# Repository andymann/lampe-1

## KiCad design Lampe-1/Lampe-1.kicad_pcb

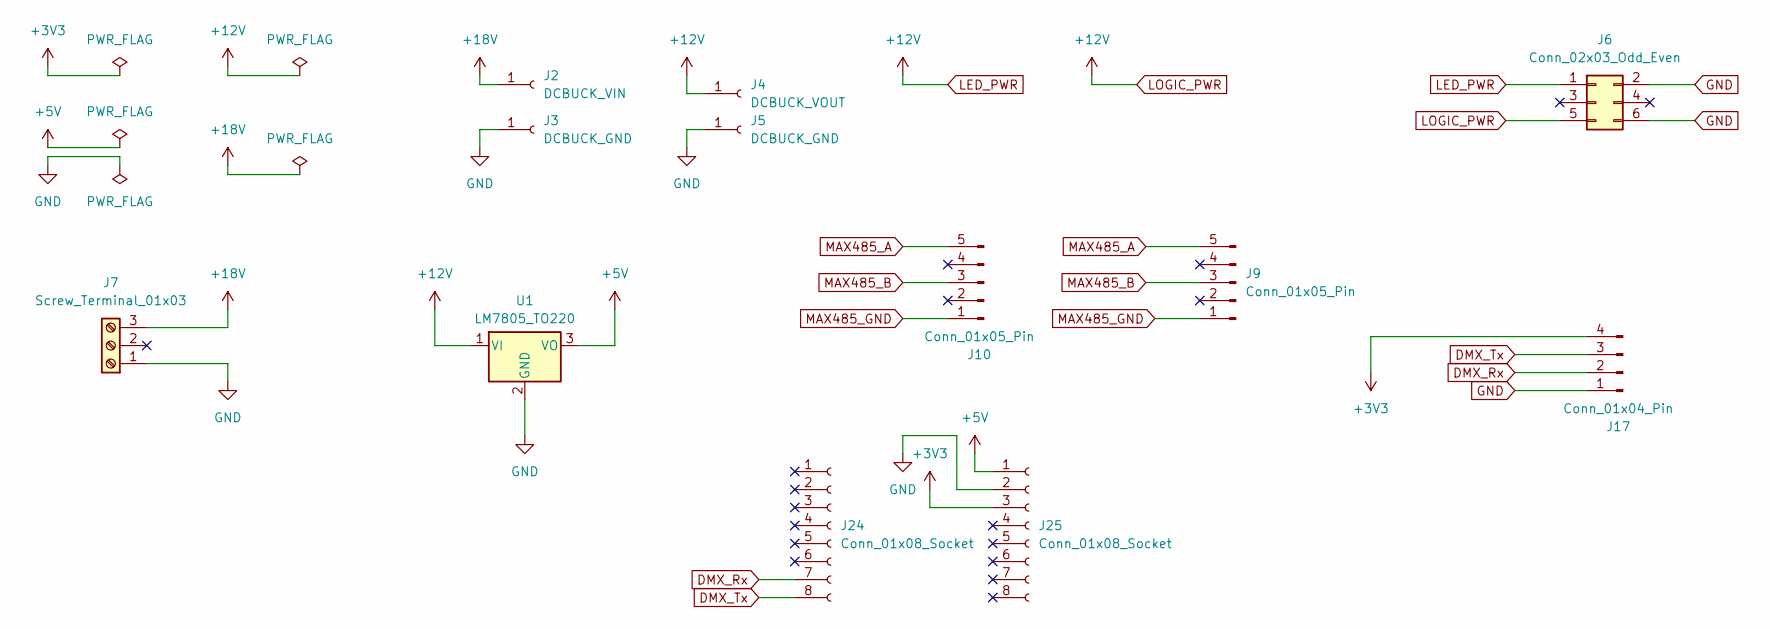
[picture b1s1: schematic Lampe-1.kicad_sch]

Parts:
J2: DCBUCK_VIN; PinHeader_1x01_P2.54mm_Vertical
J3, J5: DCBUCK_GND; PinHeader_1x01_P2.54mm_Vertical
J4: DCBUCK_VOUT; PinHeader_1x01_P2.54mm_Vertical
J6: Conn_02x03_Odd_Even; PinSocket_2x03_P2.54mm_Vertical
J7: Screw_Terminal_01x03; PinHeader_1x03_P2.54mm_Vertical
J9, J10: Conn_01x05_Pin; PinHeader_1x05_P2.54mm_Vertical
J17: Conn_01x04_Pin; PinHeader_1x04_P2.54mm_Vertical
J24, J25: Conn_01x08_Socket; PinHeader_1x08_P2.54mm_Vertical
U1: LM7805_TO220; TO-220-3_Vertical

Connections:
+3V3: J17.4, J25.3
+5V: J25.1, U1.3 (VO)
+18V: J2.1 (Pin_1_1), J7.3
DMX_Rx: J17.2, J24.7
DMX_Tx: J17.3, J24.8
GND: J3.1 (Pin_1_1), J5.1 (Pin_1_1), J6.2, J6.6, J7.1, J17.1, J25.2, U1.2 (GND)
LED_PWR: J4.1 (Pin_1_1), J6.1, J6.5, U1.1 (VI)
MAX485_A: J9.5, J10.5
MAX485_B: J9.3, J10.3
MAX485_GND: J9.1, J10.1

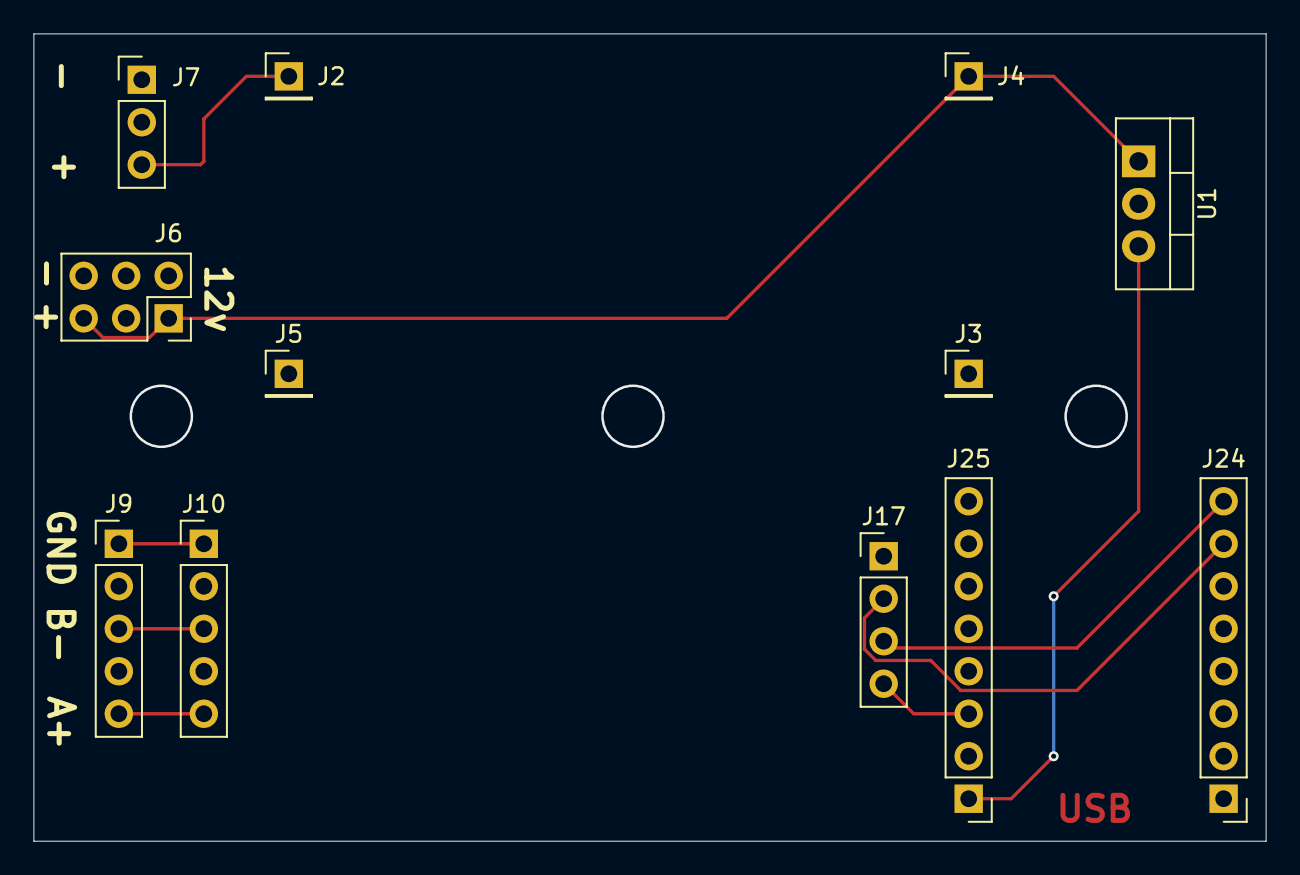
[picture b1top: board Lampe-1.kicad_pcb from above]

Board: 2 copper layers, 73.7 x 48.3 mm, 12 parts (0 on the bottom side), 10 nets.
